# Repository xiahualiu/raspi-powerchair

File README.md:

# Raspi-powerchair

The code inside this reporsitory allows a Raspberry Pi 4B model to control the Pride ES powerchair directly by simulating the original handle controller. The initial purpose of this project is to custom the existing electric wheeler to work as a mobile robot.

Also, the DC motor driver board design can be found under the `hardware` folder.

## Hardware Requirements

* Any Raspberry Pi 4B model.
* DJI M2006 Brushless Motor
* DJI C610 Speed Controller
 
## Software Requirements

* Ubuntu Server 20.04 for Pi
* ROS Noetic
* GCC
* G++
* cmake
* make
* spidev >= 3.5

Please ensure the SPI devices are enabled in the `raspi-config`, or you add `dtparam=spi=on` in the `/boot/config.txt` file.

For the schematics and PCB viewing and editing, [KiCad](https://kicad.org/) is required.  

## Disclaimer

The code and circuit design inside this repository should not be used outside the researching laboratory since it does not contain any safety regulations like the factory one. Please be adviced, using the code inside this repository means you understand the hidden safe risks and are well prepared for it, I shall take no responsibility for the damage it may cause.

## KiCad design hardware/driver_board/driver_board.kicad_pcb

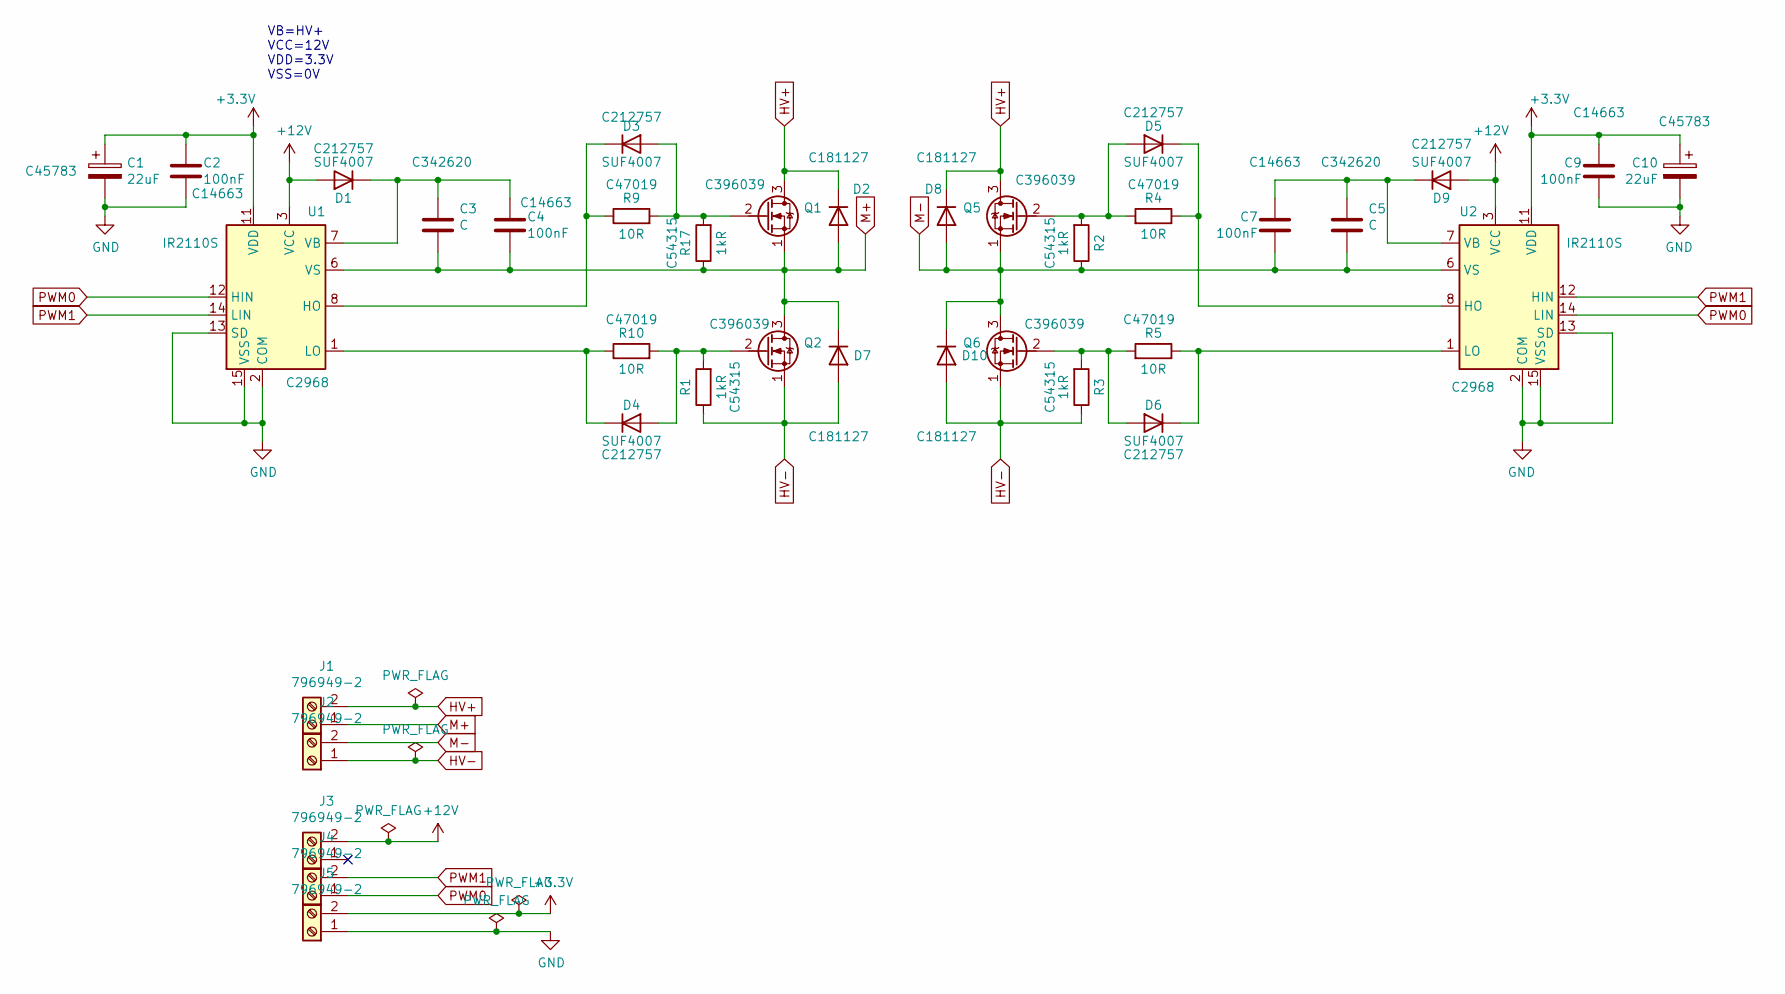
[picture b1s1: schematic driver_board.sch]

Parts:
C1, C10: 22uF; C_0805_2012Metric; LCSC C45783
C2, C4, C7, C9: 100nF; C_0603_1608Metric; LCSC C14663
C3, C5: C; C_1206_3216Metric; LCSC C342620
D1, D3, D4, D5, D6, D9: SUF4007; D_MELF; LCSC C212757
D2, D7, D8, D10: 1N4007; D_SOD-123F; LCSC C181127
J1, J2, J3, J4, J5: 796949-2; TerminalBlock_Phoenix_MKDS-1,5-2-5.08_1x02_P5.08mm_Horizont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
Q1, Q2, Q5, Q6: TPH4R008NH,L1Q(M; SOP-8-1EP_4.57x4.57mm_P1.27mm_EP4.57x4.45mm_ThermalVias; LCSC C396039
R1, R2, R3, R17: 1kR; R_2512_6332Metric; LCSC C54315
R4, R5, R9, R10: 10R; R_2512_6332Metric; LCSC C47019
U1, U2: IR2110S; SOIC-16W_7.5x10.3mm_P1.27mm_R90; LCSC C2968

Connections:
+3V3: C1.1, C2.1, C9.1, C10.1, J5.2, U1.11 (VDD), U2.11 (VDD)
+12V: D1.2 (A), D9.2 (A), J3.2, U1.3 (VCC), U2.3 (VCC)
GND: C1.2, C2.2, C9.2, C10.2, J5.1, U1.2 (COM), U1.13 (SD), U1.15 (VSS), U2.2 (COM), U2.13 (SD), U2.15 (VSS)
HV+: D2.1 (K), D8.1 (K), J1.2, Q1.3 (D), Q5.3 (D)
HV-: D7.2 (A), D10.2 (A), J2.1, Q2.1 (S), Q6.1 (S), R1.1, R3.1
M+: C3.2, C4.2, D2.2 (A), D7.1 (K), J1.1, Q1.1 (S), Q2.3 (D), R17.1, U1.6 (VS)
M-: C5.2, C7.2, D8.2 (A), D10.1 (K), J2.2, Q5.1 (S), Q6.3 (D), R2.1, U2.6 (VS)
unnamed: C3.1, C4.1, D1.1 (K), U1.7 (VB)
unnamed: C5.1, C7.1, D9.1 (K), U2.7 (VB)
unnamed: D3.1 (K), R9.1, U1.8 (HO)
unnamed: D3.2 (A), Q1.2 (G), R9.2, R17.2
unnamed: D4.1 (K), R10.1, U1.1 (LO)
unnamed: D4.2 (A), Q2.2 (G), R1.2, R10.2
unnamed: D5.1 (K), R4.1, U2.8 (HO)
unnamed: D5.2 (A), Q5.2 (G), R2.2, R4.2
unnamed: D6.1 (K), R5.1, U2.1 (LO)
unnamed: D6.2 (A), Q6.2 (G), R3.2, R5.2
PWM0: J4.1, U1.12 (HIN), U2.14 (LIN)
PWM1: J4.2, U1.14 (LIN), U2.12 (HIN)

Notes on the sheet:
VB=HV+ VCC=12V VDD=3.3V VSS=0V

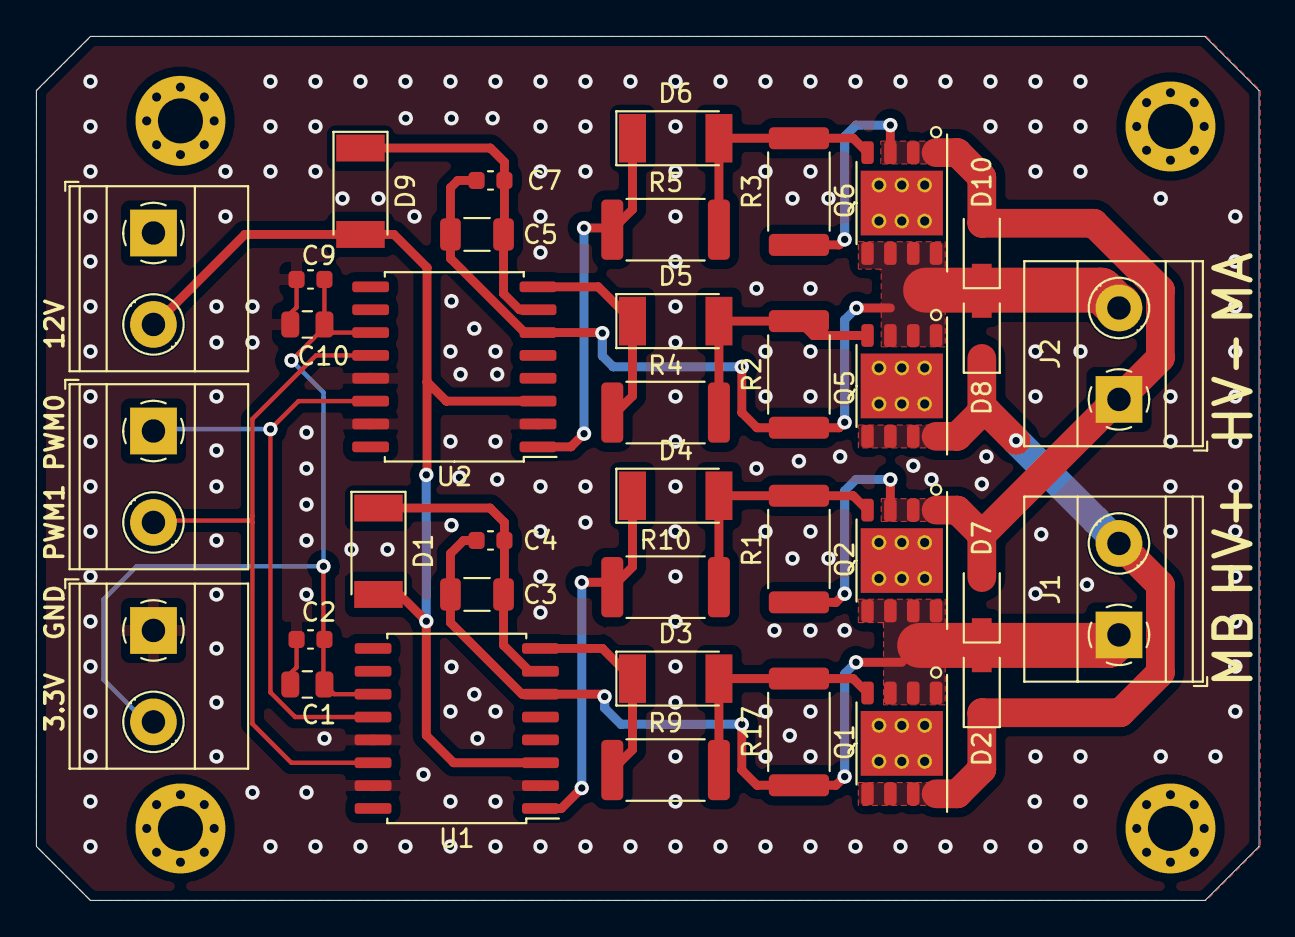
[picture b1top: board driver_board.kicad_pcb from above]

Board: 2 copper layers, 67.9 x 48.0 mm, 37 parts (0 on the bottom side), 19 nets.

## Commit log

2020-11-03 Add the protocol manual.
2020-11-04 Revise the protocol manual.
2021-02-11 update PCB
2021-02-11 update final
2021-02-11 update pdf outputs
2021-03-04 final update
2021-04-27 Add new catkin_worksapce and mcp2515 package
2021-04-28 MCP2515 CAN TX function tested.
2021-04-28 Modified README; add .gitignore
2021-04-29 Update mcp2515_node.py
    Fixed: Some of the comments have grammar issues and are not consistent to the code itself.
2021-04-30 Update mcp2515_node.py
    Add can read function.
